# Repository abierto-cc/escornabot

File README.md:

# furubot

Diseño de robot basado en el Escornabot, completamente hecho en KiCAD. 

Con amor para todo el mundo desde Malmo - Suecia.

# créditos

Los creadores originales de Escornabot www.escornabot.com y su comunidad de usuarios y desarrolladores 

# autor

J. Garcia at abierto.cc

# abierto

Abierto es una inciativa de D. Cuartielles gracias a la generosa aportación de la Fundación PUIG por intermediación de la Fundación Ashoka de cara a contribuir a la creación de material educativo de libre acceso y circulación
/
├── audit_repo.sh
├── .github/
│   └── workflows/
│       └── auditoria.yml
└── (resto del proyecto)
repo_audit/REPORTE.md
name: Auditoría Integral del Repositorio

on:
  workflow_dispatch:
  push:
    branches:
      - master

jobs:
  audit:
    runs-on: ubuntu-latest

    steps:
      - name: Checkout del repositorio
        uses: actions/checkout@v4

      - name: Crear carpeta de salida
        run: mkdir -p repo_audit

      - name: Ejecutar script de auditoría
        run: bash audit_repo.sh

      - name: Generar reporte en Markdown
        run: |
          echo "# Reporte de Auditoría del Repositorio" > repo_audit/REPORTE.md
          echo "Generado automáticamente por GitHub Actions." >> repo_audit/REPORTE.md
          echo "" >> repo_audit/REPORTE.md
          echo "## Extensiones encontradas" >> repo_audit/REPORTE.md
          cat repo_audit/extensions.txt >> repo_audit/REPORTE.md
          echo "" >> repo_audit/REPORTE.md
          echo "## Total de archivos por extensión" >> repo_audit/REPORTE.md
          for f in repo_audit/*.txt; do
            if [[ "$f" != *"extensions.txt"* && "$f" != *"sha256sums.txt"* && "$f" != *"sizes.txt"* ]]; then
              ext=$(basename "$f" .txt)
              count=$(wc -l < "$f")
              echo "- **$ext**: $count archivos" >> repo_audit/REPORTE.md
            fi
          done

      - name: Subir artefactos de auditoría
        uses: actions/upload-artifact@v4
        with:
          name: auditoria-completa
          path: repo_audit/

      # OPCIONAL: Notificación por Slack
      # - name: Notificar a Slack
      #   uses: slackapi/slack-github-action@v1.24.0
      #   with:
      #     payload: |
      #       {
      #         "text": "✅ Auditoría completada en el repositorio."
      #       }
      #   env:
      #     SLACK_WEBHOOK_URL: ${{ secrets.SLACK_WEBHOOK_URL }}

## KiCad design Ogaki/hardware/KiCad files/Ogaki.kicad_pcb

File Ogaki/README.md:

# Escornabot Ogaki

Diseño de robot basado en el Escornabot, completamente hecho en KiCAD. 

Con amor para todo el mundo desde Malmo - Suecia.

# consigue tu kit

Si quieres conseguir el kit para montarlo, visita: https://abierto.cc/shop

# instrucciones de montaje

Puedes ver las instrucciones de montaje paso a paso en: https://sites.google.com/abierto.cc/ogaki

# créditos

Los creadores originales de Escornabot y su comunidad de usuarios y desarrolladores

# autor

J. Garcia at abierto.cc

# abierto

Abierto es una inciativa de D. Cuartielles gracias a la generosa aportación de la Fundación PUIG por intermediación de la Fundación Ashoka de cara a contribuir a la creación de material educativo de libre acceso y circulación

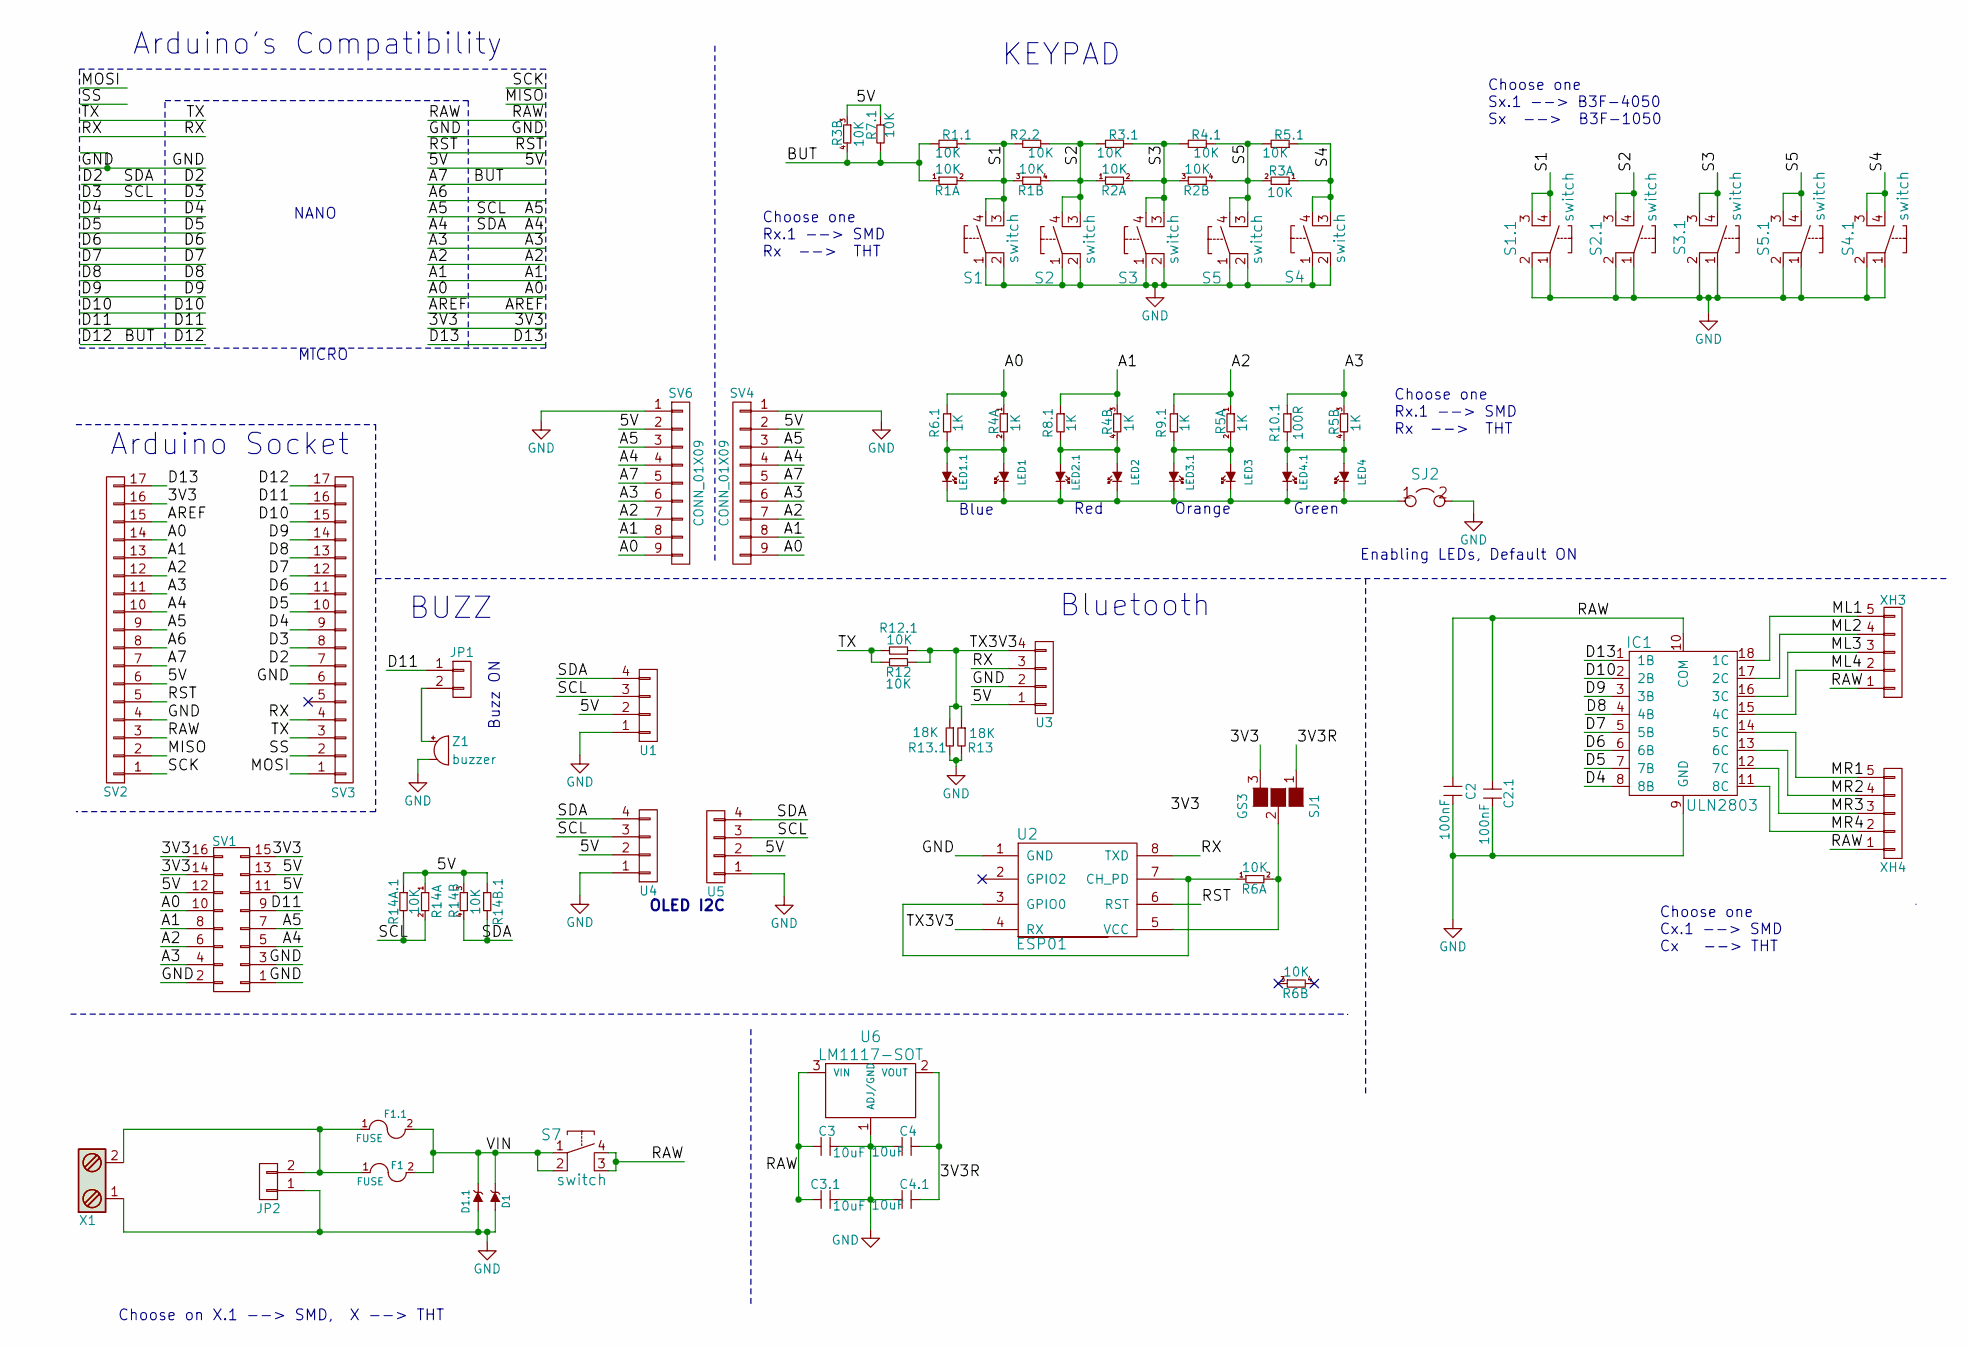
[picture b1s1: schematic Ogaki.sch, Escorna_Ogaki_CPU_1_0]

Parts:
C2: 100nF; C_Disc_D5.0mm_W2.5mm_P5.00mm
C2.1: 100nF; C_0603_HandSoldering
C3, C4: 10uF; C_Disc_D5.0mm_W2.5mm_P5.00mm
C3.1, C4.1: 10uF; C_0603_HandSoldering
D1: ZENER; D_DO-41_SOD81_P10.16mm_Horizontal
D1.1: ZENER; D_0603
F1: FUSE; Fuse_TE5_Littlefuse-395Series
F1.1: FUSE; R_1206_HandSoldering
IC1: ULN2803; DIP-18_W7.62mm_Socket
JP1: CONN_01X02; Pin_Header_Straight_1x02_Pitch2.54mm
JP2: CONN_01X02; Pin_Header_Angled_1x02_Pitch2.54mm
LED1, LED2, LED3, LED4: L; LED_D3.0mm
LED1.1, LED2.1, LED3.1, LED4.1: L; LED_0603
R1, R2, R3, R6, R14: 10K; R_Array_SIP4
R1.1, R2.2, R3.1, R4.1, R5.1, R7.1, R12.1, R14A.1, R14B.1: 10K; R_0603_HandSoldering
R4, R5: 1K; R_Array_SIP4
R6.1, R8.1, R9.1: 1K; R_0603_HandSoldering
R10.1: 100R; R_0603_HandSoldering
R12: 10K; R_Axial_DIN0204_L3.6mm_D1.6mm_P7.62mm_Horizontal
R13: 18K; R_Axial_DIN0204_L3.6mm_D1.6mm_P7.62mm_Horizontal
R13.1: 18K; R_0603_HandSoldering
S1, S2, S3, S4, S5: switch; Button
S1.1, S2.1, S3.1, S4.1, S5.1: switch; SW_PUSH_6mm
S7: switch; on_off_Switch
SJ1: GS3
SJ2: JUMPER; GS2
SV1: CONN_02X08; Pin_Header_Straight_2x08_Pitch2.54mm
SV2, SV3: CONN_01X17; Pin_Header_Straight_1x17_Pitch2.54mm
SV4, SV6: CONN_01X09; Pin_Header_Straight_1x09_Pitch2.54mm
U1, U3, U4, U5: CONN_01X04; Pin_Header_Straight_1x04_Pitch2.54mm
U2: ESP01
U6: LM1117-SOT; TO-220_Vertical
X1: Screw_Terminal_1x02; bornier2
XH3, XH4: CONN_01X05; B5B-XH-A
Z1: buzzer; MagneticBuzzer_StarMicronics_HMB-06_HMB-12

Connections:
/3V3: SJ1.3 (G3), SV1.14, SV1.15, SV1.16, SV2.16
/3V3R: C4.1, C4.1.1, SJ1.1 (G1), U6.2 (VOUT)
/5V: R3.3, R7.1.1, R14.1, R14.3, R14A.1.1, R14B.1.1, SV1.11, SV1.12, SV1.13, SV2.6, SV4.2, SV6.2, U1.2, U3.1, U4.2, U5.2
/A0: R4.1, R6.1.1, SV1.10, SV2.14, SV4.9, SV6.9
/A1: R4.3, R8.1.1, SV1.8, SV2.13, SV4.8, SV6.8
/A2: R5.1, R9.1.1, SV1.6, SV2.12, SV4.7, SV6.7
/A3: R5.3, R10.1.1, SV1.4, SV2.11, SV4.6, SV6.6
/A4: R14.4, R14B.1.2, SV1.5, SV2.10, SV3.7, SV4.4, SV6.4, U1.4, U4.4, U5.4
/A5: R14.2, R14A.1.2, SV1.7, SV2.9, SV3.8, SV4.3, SV6.3, U1.3, U4.3, U5.3
/A6: SV2.8
/A7: R1.1, R1.1.2, R3.4, R7.1.2, SV2.7, SV3.17, SV4.5, SV6.5
/AREF: SV2.15
/D4: IC1.8 (8B), SV3.9
/D5: IC1.7 (7B), SV3.10
/D6: IC1.6 (6B), SV3.11
/D7: IC1.5 (5B), SV3.12
/D8: IC1.4 (4B), SV3.13
/D9: IC1.3 (3B), SV3.14
/D10: IC1.2 (2B), SV3.15
/D11: JP1.1, SV1.9, SV3.16
/D13: IC1.1 (1B), SV2.17
/MISO: SV2.2
/ML1: IC1.18 (1C), XH3.5
/ML2: IC1.17 (2C), XH3.4
/ML3: IC1.16 (3C), XH3.3
/ML4: IC1.15 (4C), XH3.2
/MOSI: SV3.1
/MR1: IC1.14 (5C), XH4.5
/MR2: IC1.13 (6C), XH4.4
/MR3: IC1.12 (7C), XH4.3
/MR4: IC1.11 (8C), XH4.2
/RAW: C2.2, C2.1.2, C3.2, C3.1.2, IC1.10 (COM), S7.3, S7.4, SV2.3, U6.3 (VIN), XH3.1, XH4.1
/RST: SV2.5, U2.6 (RST)
/RX: SV3.4, U2.8 (TXD), U3.3
/S1: R1.2, R1.3, R1.1.1, R2.2.2, S1.3, S1.4, S1.1.3, S1.1.4
/S2: R1.4, R2.1, R2.2.1, R3.1.2, S2.3, S2.4, S2.1.3, S2.1.4
/S3: R2.2, R2.3, R3.1.1, R4.1.2, S3.3, S3.4, S3.1.3, S3.1.4
/S4: R3.1, R5.1.1, S4.3, S4.4, S4.1.3, S4.1.4
/S5: R2.4, R3.2, R4.1.1, R5.1.2, S5.3, S5.4, S5.1.3, S5.1.4
/SCK: SV2.1
/SS: SV3.2
/TX: R12.2, R12.1.2, SV3.3
/TX3V3: R12.1, R12.1.1, R13.1, R13.1.1, U2.4 (RX), U3.4
/VIN: D1.1 (K), D1.1.1 (K), F1.2, F1.1.2, S7.1, S7.2
GND: C2.1, C2.1.1, C3.1, C3.1.1, C4.2, C4.1.2, D1.2 (A), D1.1.2 (A), IC1.9 (GND), JP2.1, R13.2, R13.1.2, S1.1, S1.2, S1.1.1, S1.1.2, S2.1, S2.2, S2.1.1, S2.1.2, S3.1, S3.2, S3.1.1, S3.1.2, S4.1, S4.2, S4.1.1, S4.1.2, S5.1, S5.2, S5.1.1, S5.1.2, SJ2.2, SV1.1, SV1.2, SV1.3, SV2.4, SV3.6, SV4.1, SV6.1, U1.1, U2.1 (GND), U3.2, U4.1, U5.1, U6.1 (ADJ/GND), X1.1, Z1.2; also elsewhere on the board
unnamed: F1.1, F1.1.1, JP2.2, X1.2
unnamed: JP1.2, Z1.1
unnamed: LED1.1 (K), LED1.1.1 (K), LED2.1 (K), LED2.1.1 (K), LED3.1 (K), LED3.1.1 (K), LED4.1 (K), LED4.1.1 (K), SJ2.1
unnamed: LED1.2 (A), LED1.1.2 (A), R4.2, R6.1.2
unnamed: LED2.2 (A), LED2.1.2 (A), R4.4, R8.1.2
unnamed: LED3.2 (A), LED3.1.2 (A), R5.2, R9.1.2
unnamed: LED4.2 (A), LED4.1.2 (A), R5.4, R10.1.2
unnamed: R6.1, U2.3 (GPIO0), U2.7 (CH_PD)
unnamed: R6.2, SJ1.2 (G2), U2.5 (VCC)

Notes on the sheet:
MICRO
NANO
Arduino's Compatibility
Arduino Socket
Choose one Rx.1 --> SMD Rx --> THT
Choose one Sx.1 --> B3F-4050 Sx --> B3F-1050
KEYPAD
Enabling LEDs, Default ON
BUZZ
Buzz ON
OLED I2C
Bluetooth
Choose one Cx.1 --> SMD Cx --> THT
Choose on X.1 --> SMD, X --> THT
Blue
Red
Orange
Green

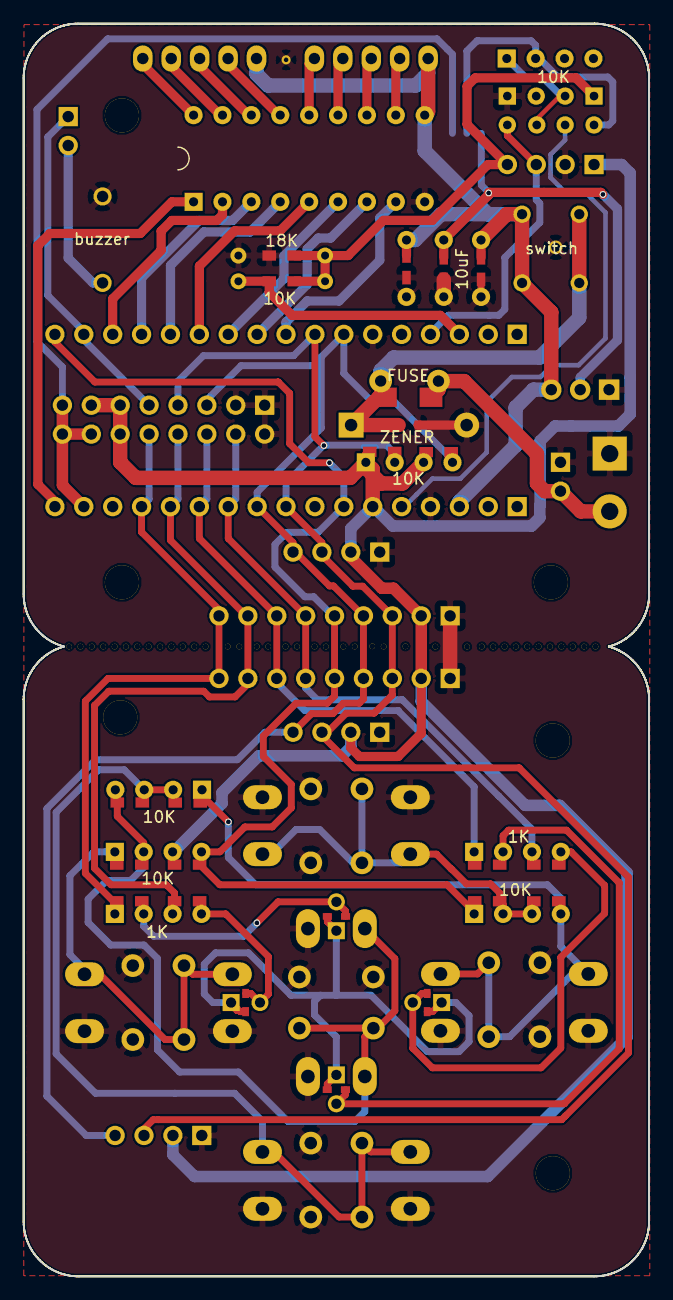
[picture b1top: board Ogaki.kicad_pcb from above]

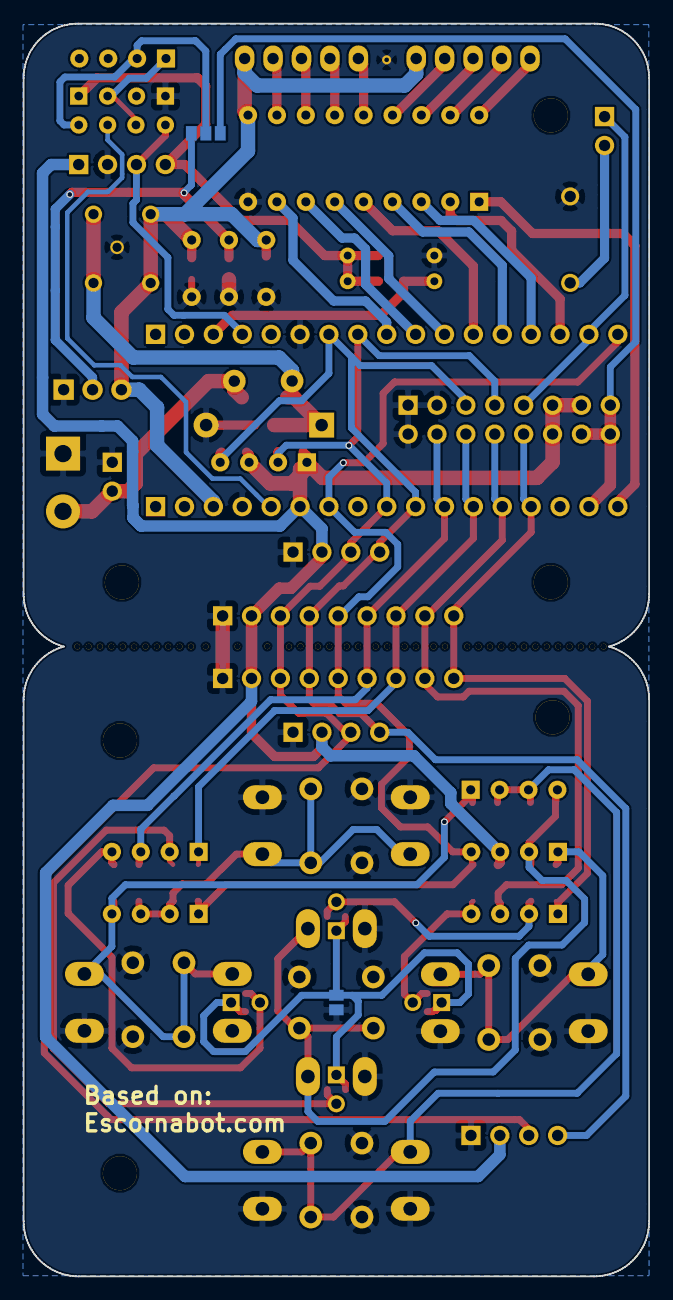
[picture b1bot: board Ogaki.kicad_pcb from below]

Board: 2 copper layers, 55.0 x 110.1 mm, 75 parts (3 on the bottom side), 48 nets.

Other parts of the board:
GND: GND; SolderWirePad_single_0-8mmDrill
svg2mod, svg2mod#2: G***; svg2mod

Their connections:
GND: GND.1; also elsewhere on the board

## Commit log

2017-04-07 Fixed readme
2017-04-07 Añadidos ficheros de diseño
2017-04-07 revised folder structure
2017-04-07 deleted old files
2017-04-07 fixed folder name
2017-04-07 Actualización del fichero de layout con las cotas de los drills para la fijacion
2017-04-07 moved readme to base folder
2017-04-24 Actualizacion hardware
    Corrección de errores
2017-04-25 Actualización de hardware
2017-05-05 Actualizacion hardware
2017-05-05 Actualización hardware
2017-05-24 Actualización a Egaki
2017-09-15 Firmware Furubot
    Adaptación del código de Escornabot para la versión Ogaki
2017-10-17 Actualización a la version Ogaki
2017-10-17 Esquemáticos
    Archivos png y pdf de los esquemáticos del Joselito mini
2017-10-17 Silks
    Archivos de borde de placa en formato de componente para KiCad
2017-10-17 Actualización a la verison Ogaki
2017-10-17 Esquemáticos
    Archivos png y pdf de los esquemáticos del Escornabot Ogaki
2017-10-17 Dimensiones
    Archivos de borde de placa en formato de componente para KiCad
2017-10-17 KiCad files
    Archivos de diseño en KiCad del Escornabot Ogaki
2017-10-17 Gerbers
    Archivos para fabricación de PCB delEscornabot Ogaki
2017-10-17 Firmware
    Adaptación del código original de Escornabot a la versión Ogaki
2017-10-19 BOM Ogaki
    Lista de los componentes necesarios para el montaje completo de la electrónica de la versión Ogaki de Escornabot
2017-10-19 Furubot
2017-10-19 BOM Ogaki
    Lista de componentes para la versión Ogaki de Escornabot
2017-10-19 BOM Ogaki
2017-10-19 Actualizado el Readme... Amigos!!
2017-10-19 Actualizado el Readme
2017-10-21 added 3D models
2017-10-21 added source files for 3d models
2017-10-31 Esquemas
    Archivos png y pdf de los esquemas del Escornabot Ogaki
2017-11-23 Conexiones
    Archivo con las conexiones de los componentes de Ogaki para Arduino Micro y Arduino Nano
2017-11-24 Actualización de software
    Añadido el software para Ogaki con Arduino Nano
2018-02-07 Instrucciones de montaje del chasis
    Hemos añadido un documento con las instruccionesde montaje del chasis de Ogaki
2018-02-07 Instrucciones de montaje del chasis
    Documento con las instruccionesde montaje del chasis de Ogaki
2018-02-14 Update Configuration.h
    SIMPLE_LED_PIN y BUZZER_PIN, utilizan el mismo PIN, por lo que el buzzer no para de pitar :)
2019-02-05 adafruit motor changes
2019-02-05 Update Configuration.h
    Updated
2019-02-05 Update Configuration.h
    Added missing row
2025-12-17 README Update file organization scripts and add output files # # On branch master # Your branch is up to date with 'origin/master'. # # Changes to be committed: # modified: README.md # new file: all_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

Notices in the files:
Ogaki/hardware/KiCad files/Ogaki.kicad_pcb:
Attribution-ShareAlike 4.0 International (CC BY-SA 4.0)
